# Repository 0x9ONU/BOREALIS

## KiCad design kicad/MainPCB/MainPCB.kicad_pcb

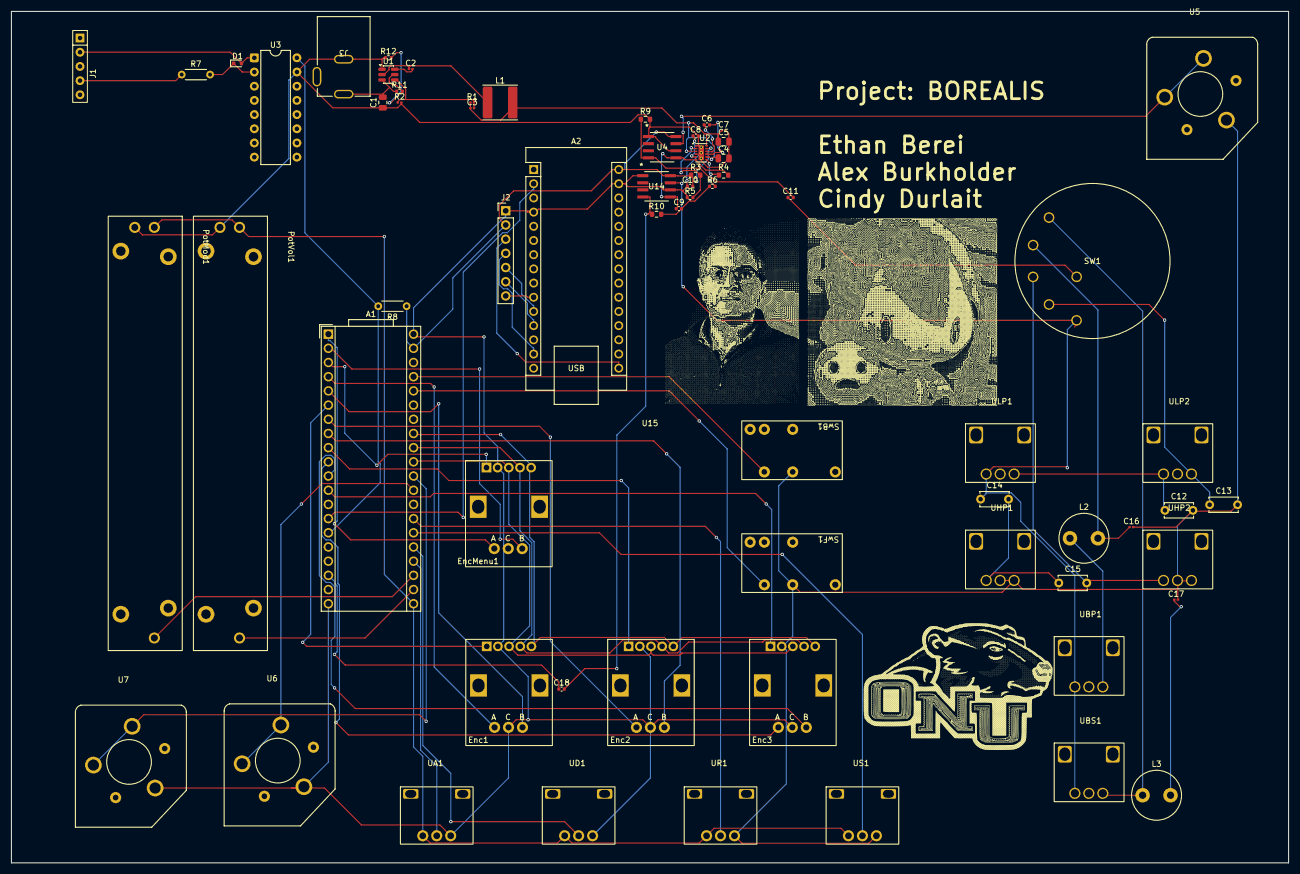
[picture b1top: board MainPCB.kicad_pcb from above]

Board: 2 copper layers, 228.6 x 152.4 mm, 67 parts (0 on the bottom side), 64 nets.

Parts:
A1: Electrosmith_Daisy_Seed_Rev4; Electrosmith_Daisy_Seed
A2: Arduino_Nano_Every; Arduino_Nano
C1: 10uF; C_0805_2012Metric
C2, C16, C17: 100nF; C_0201_0603Metric
C3: 10nF; C_0201_0603Metric
C4, C5: 22uF; C_0805_2012Metric
C6, C9, C10, C11, C18: 1uF; C_0402_1005Metric
C7: 2.2uF; C_0201_0603Metric
C8: 4.7uF; C_0402_1005Metric
C12, C13, C14, C15: 10nF; C_Disc_D5.0mm_W2.5mm_P5.00mm
D1: 1N4148WT; D_SOD-523
Enc1, Enc2, Enc3: Encoder
EncMenu1: Encoder
J1: DIN-5; R_Array_SIP5
J2: Conn_01x07_Pin; PinHeader_1x07_P2.54mm_Vertical
J3: 54-00166; CONN3_54-00166_TEN
L1: 4.7uH; L_APV_ANR6028
L2, L3: 10mH; L_Radial_D8.7mm_P5.00mm_Fastron_07HCP
PotMod1: Slide Pot
PotVol1: Slide Pot
R1: 52.3k; R_0201_0603Metric
R2: 10k; R_0201_0603Metric
R3: 87.6k; R_0603_1608Metric
R4, R9, R10: 86.6k; R_0603_1608Metric
R5, R6, R11, R12: 50k; R_0402_1005Metric
R7: 220; R_Axial_DIN0204_L3.6mm_D1.6mm_P5.08mm_Horizontal
R8: 280; R_Axial_DIN0204_L3.6mm_D1.6mm_P5.08mm_Horizontal
SW1: KC15A9.501NPF; KC15A9.501NPF_EWI
SwB1: Untitled
SwF1: Untitled
U1: AP62250WU; TSOT-23-6
U2: LM27762; WSON-12-1EP_3x2mm_P0.5mm_EP1x2.65_ThermalVias
U3: LTV-847; DIP-16_W7.62mm
U4, U14: AD8226BRZ-RL; R_8_ADI
U5, U6, U7: Audio_Jack
U15: Top Plate
UA1: Big Pot
UBP1: Small Pot
UBS1: Small Pot
UD1: Big Pot
UHP1, UHP2: Small Pot
ULP1, ULP2: Small Pot
UR1: Big Pot
US1: Big Pot

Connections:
/Amplification/Audio_In: C11.1, SW1.A
/Amplification/Audio_Out: U4.7 (VOUT), U5.3, U5.4
/Amplification/Vcc: A1.39 (VIN), A2.30 (VIN), C10.2, J2.2, R3.1, R8.1, U2.11 (OUT+), U4.8 (VS+), U14.8 (VS+)
/Amplification/Vdd: C9.1, R4.2, U2.6 (OUT-), U4.5 (VS-), U14.5 (VS-)
/Filters/Audio_In: A1.18 (AUDIO_OUT_1), C18.1
/Filters/Band Pass/Audio_In: C14.1, SW1.1, U14.7 (VOUT), UBP1.1, UBS1.1, ULP1.1
/Filters/Band Pass/Audio_Out: C16.1, L2.2, SW1.4
/Filters/Band Stop/Audio_Out: L3.1, SW1.5, UBS1.3
/Filters/High Pass/Audio_Out: C15.2, SW1.3, UHP2.1
/Filters/Low Pass/Audio_Out: C13.1, SW1.2, ULP2.3
/Menu Controls/1_A: A1.4 (SD_DATA_1), Enc1.A
/Menu Controls/1_B: A1.5 (SD_DATA_0), Enc1.B
/Menu Controls/1_Button: A1.6 (SD_CMD), Enc1.1
/Menu Controls/2_A: A1.7 (SD_CLK), Enc2.A
/Menu Controls/2_B: A1.8 (SPI1_CS), Enc2.B
/Menu Controls/2_Button: A1.9 (SPI1_SCK), Enc2.1
/Menu Controls/3.3A: A1.21 (3V3_A), PotMod1.1, PotVol1.1, UA1.1, UD1.1, UR1.1, US1.1
/Menu Controls/3_A: A1.10 (SPI1_POCI), Enc3.A
/Menu Controls/3_B: A1.11 (SPI1_PICO), Enc3.B
/Menu Controls/3_Button: A1.12 (I2C1_SCL), Enc3.1
/Menu Controls/B: A1.33 (SAI2_SD_A), Enc1.5 (B), Enc2.5 (B), Enc3.5 (B), EncMenu1.5 (B)
/Menu Controls/Back: A1.37 (USB_D_+), SwB1.4 (N.O.)
/Menu Controls/CV_Gate_1: A1.29 (DAC_OUT2), U6.3, U6.4
/Menu Controls/CV_Gate_2: A1.30 (DAC_OUT1), U7.3, U7.4
/Menu Controls/Daisy_TX: A1.14 (USART1_TX), A2.2 (RX1)
/Menu Controls/Forward: A1.36 (USB_D_-), SwF1.4 (N.O.)
/Menu Controls/G: A1.32 (SAI2_SD_B), Enc1.4 (G), Enc2.4 (G), Enc3.4 (G), EncMenu1.4 (G)
/Menu Controls/MIDI: A1.15 (USART1_RX), R8.2, U3.16
/Menu Controls/Menu_A: A1.1 (USB_ID), EncMenu1.A
/Menu Controls/Menu_B: A1.2 (SD_DATA_3), EncMenu1.B
/Menu Controls/Menu_Button: A1.3 (SD_DATA_2), EncMenu1.1
/Menu Controls/R: A1.31 (SAI2_MCLK), Enc1.3 (R), Enc2.3 (R), Enc3.3 (R), EncMenu1.3 (R)
/Midi Input/DIN 2: D1.2 (A), J1.2, U3.1
/Midi Input/DIN 4: J1.4, R7.1
/Power/+5V: C3.1, C4.1, C5.1, C7.1, L1.2, R1.1, U2.3 (VIN), U2.8 (EN-), U2.12 (EN+)
/Power/+9V: C1.2, J3.A, R11.1, U1.3 (VIN)
GND: A1.20 (AGND), A1.40 (DGND), A2.4 (GND), A2.29 (GND), C1.1, C4.2, C5.2, C7.2, C8.2, C9.2, C10.1, C12.2, C13.2, C16.2, C17.2, Enc1.2, Enc1.C, Enc2.2, Enc2.C, Enc3.2, Enc3.C, EncMenu1.2, EncMenu1.C, J2.1, J3.B, PotMod1.2, PotVol1.2, R2.2, R5.1, R6.1, R9.2, R10.2, R12.1, SwB1.1, SwF1.1, U1.1 (GND), U2.1 (PGOOD), U2.4 (GND), U2.13 (PAD), U3.15, U4.1 (IN-), U4.6 (REF), U5.1, U6.1, U7.1, U14.1 (IN-), U14.6 (REF), UA1.3, UD1.3, UHP1.2, UHP1.3, UHP2.2, UHP2.3, UR1.3, US1.3
unnamed: A1.22 (ADC_0), PotVol1.3
unnamed: A1.23 (ADC_1), PotMod1.3
unnamed: A1.24 (ADC_2), UA1.2
unnamed: A1.25 (ADC_3), UD1.2
unnamed: A1.26 (ADC_4), US1.2
unnamed: A1.27 (ADC_5), UR1.2
unnamed: A2.10 (D7), J2.7
unnamed: A2.11 (D8), J2.5
unnamed: A2.12 (D9), J2.6
unnamed: A2.14 (MOSI), J2.4
unnamed: A2.16 (SCK), J2.3
unnamed: C12.1, ULP1.3, ULP2.1
unnamed: C14.2, C15.1, UHP1.1
unnamed: C17.1, L3.2
unnamed: D1.1 (K), R7.2, U3.2
unnamed: L2.1, UBP1.3
unnamed: C2.2, U1.6 (BST)
unnamed: R11.2, R12.2, U1.5 (EN)
unnamed: C3.2, R1.2, R2.1, U1.4 (FB)
unnamed: C2.1, L1.1, U1.2 (SW)
unnamed: C6.1, U2.10 (C+)
unnamed: C6.2, U2.9 (C-)
unnamed: C8.1, U2.5 (CP)
unnamed: R3.2, R5.2, U2.2 (FB+)
unnamed: R4.1, R6.2, U2.7 (FB-)
unnamed: C11.2, R9.1, U4.4 (IN+)
unnamed: C18.2, R10.1, U14.4 (IN+)

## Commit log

2025-10-19 Added DaisyExamples
2025-10-19 test
2025-10-24 Created a new build system
    With these changes, we can now run tasks from the root directory in vscode.
    Added the .vscode folder which creates the same task commands we all love, but added a prompt and some extra commands to each task to automatically move to the desired directory for running the task,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
2025-10-24 Renamed a test project
    Turned this copy of an example project into the Wavetable algorithm test. I'm thinking about modifying the oscillator class or making a new wavetable class to support our implementation of wavetables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
2025-10-24 Created project_template
    Created a folder that holds the basics of getting started programming in our environment. The template includes simple code for creating a sine wave output.
2025-10-24 Small updates
    Just some random changes I didn't save before pushing last time
2025-10-24 Renamed wavetable again
2025-11-05 Fixed makefile template
    The path was funny and it wouldn't build to I fixed it
2026-01-18 Wavetable Initial
    Started implementing the wavetable class based on a Matlab implementation
2026-01-19 Changed Wavetable Implementation
    Moved the frequency and index selection outside of main processing function. New variables and functions to store this info are included with the class.
    Also added testing info for a button. Press button connected to pin 28 to swap frequencies and waves. 3 waves, 4 frequencies.
2026-01-19 added 4th frequency to test
2026-01-23 Working Wavetable Prototype
    This code will generate a wavetable with 3 waves in it, sine, triangle, and square. Additionally, it will play a static wave index and a static frequency.
    To work, the Daisy Seed output must be passed to an amplifier before going to the load (speaker), as the Seed cannot output the power required during loading.
2026-01-23 berei changes
2026-01-23 It somewhat works
2026-01-29 added a ton of stuff
2026-02-04 Polyphony Working
    Rough Polyphony functionality is proven to work. make sure you use good speakers.
    Wavetables were updated such that they now hold the oscillator state information as well. Use AddNote and RemoveNote to use this feature.
    Process now processes all oscillators and returns an array containing all 8 outputs. This will likely feed directly into the envelope generator.
2026-02-17 PRB3 Demo
    This version is the version from the PRB3 demo
2026-02-20 New UI and Screen Tests
2026-02-20 Almost forgot the Arduino code
2026-02-24 Added peripheral cababilities and new packet schema
2026-02-25 New test plan project
    This new project adds print statements to characterize the performance of the audio callback, which is the most critical timing element in the system. It will eventually report statistics every 2 min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
2026-03-06 Test Project Changes
    Some small changes to the test project. This project has been tested to compare the effect on quality and latency when changing the number of samples stored in each wavetable.
2026-03-09 kicad
2026-03-22 Final Testplan
    set wavetable width to 1024 and disabled the wait for serial connection on startup
2026-03-22 Volume and WT Index
    Added code to scan the pots. Also prints the output every 5 ms. Need to figure out the pot range in code.
    Almost implemented, needs range adjustments.
2026-04-02 ADSR Functional
    ADSR is implemented and functional. Also, Volume and WT Index are in and functional.
    One small issue remains, when you play a note, then release it, the release will be overridden if another note is played in that time. This is because when you release the note, the oscillator playin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
2026-04-06 State Machine
2026-04-06 Refactored for merger
    Refactored menu ADSR variable names for better description of use
2026-04-06 New merged project
    This project combines the menu SM and wavetable implementation. It should support MIDI input, audio output, ADSR dynamic input, volume dynamic input, WT index dynamic input, menu SM implementation, a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
